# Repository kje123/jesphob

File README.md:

# jesphob
A fork of the PhobGCC project, created for the JESNET Gamecube Controller

If you've stumbled upon this, congrats! You have found this earlier than intended. This project is currently in the prototyping phase, so I do not recommend using this until I have done an official release, and I cannot help you if weird issues pop up.

If you wanna ask me questions or get involved, you can find me on Discord. My username is .kje

Original PhobGCC project here: https://github.com/PhobGCC

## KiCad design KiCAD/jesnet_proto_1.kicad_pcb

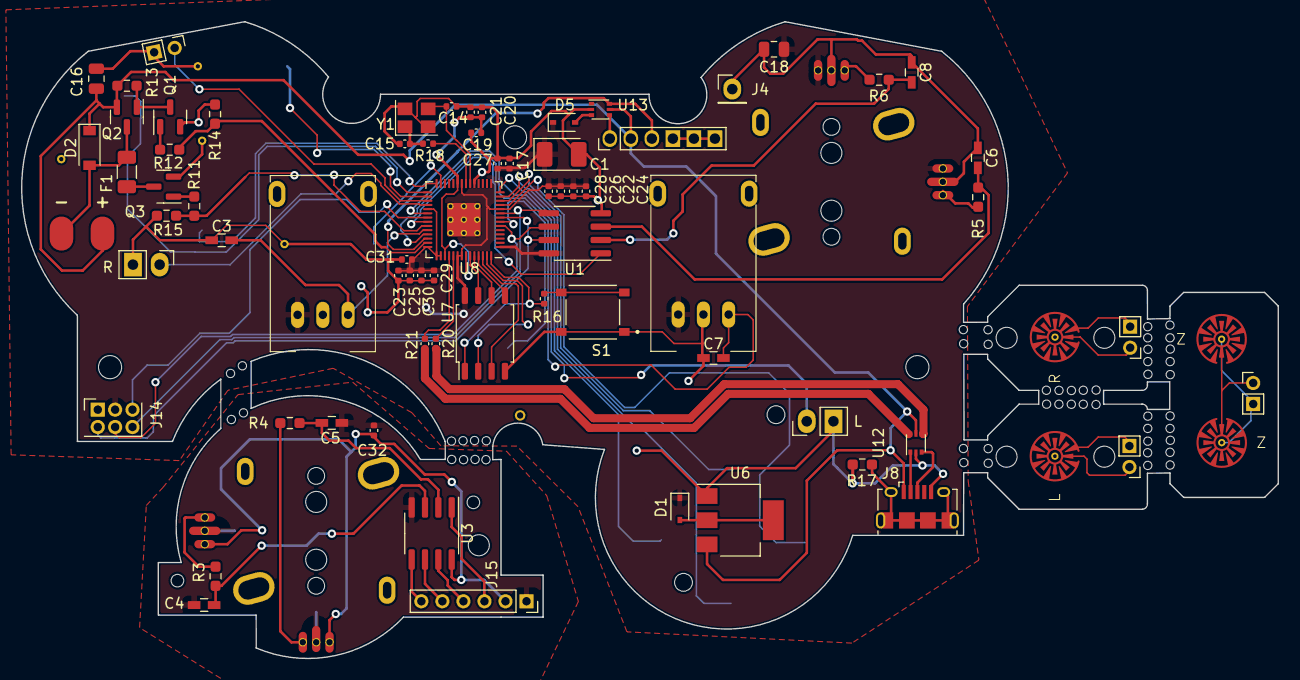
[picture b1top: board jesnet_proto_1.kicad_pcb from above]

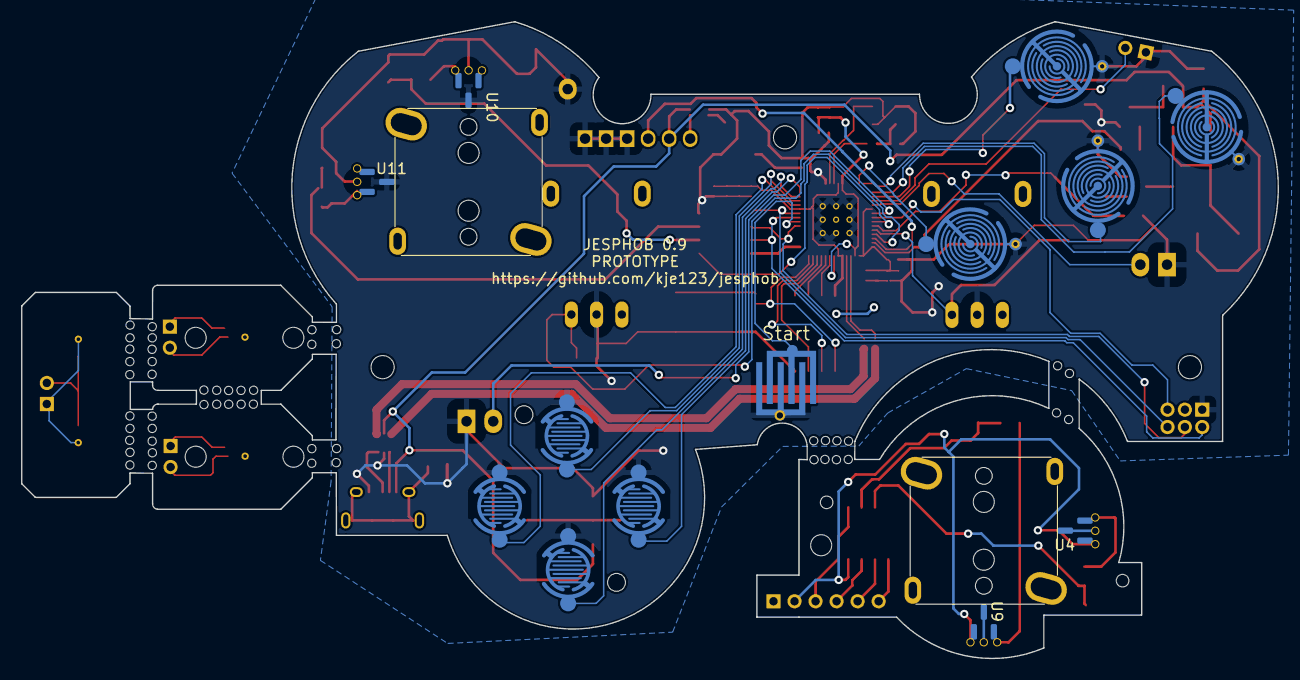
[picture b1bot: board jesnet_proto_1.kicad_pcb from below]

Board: 2 copper layers, 119.5 x 60.6 mm, 95 parts (15 on the bottom side), 65 nets.

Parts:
C1: 47u; CP_EIA-3528-12_Kemet-T_Pad1.50x2.35mm_HandSolder
C3, C4, C5, C6, C7, C8: 0.047u; C_0603_HandSoldering
C14, C15: 27p; C_0402_1005Metric
C16, C18: 10u; C_0805_2012Metric
C17, C19, C20, C22, C24, C25, C26, C27, C28, C29, C30, C31, C32: 100n; C_0402_1005Metric
C21, C23: 1u; C_0402_1005Metric
D1, D5: CUS10S30,H3F; D_SOD-323
D2: M7C; D_SOD-123
F1: Fuse; Fuse_1206_3216Metric
H5: 1.7mm; MountingHole_1.8mm
H9, H9#2, H9#3: 2.2mm; MountingHole_2.2mm
H10: 2mm; MountingHole_1.8mm
H10#2: 1.2mm; MountingHole_1.8mm
J1: Conn_01x06_Female; GCC_Header_Straight_1x06_Pitch2.00mm
J3, J3#2, J3#3, J3#4: Conn_01x02; PinHeader_1x02_P2.00mm_Horizontal
J4: Conn_01x01; PinHeader_1x01_P2.54mm_Vertical
J5: Rumble; rumble_pins
J8: USB_B_Micro; USB_Micro-B_Amphenol_10118194_Horizontal
J14, J15: Conn_01x06; PinSocket_1x06_P2.00mm_Vertical
Q1, Q3: Q_NMOS_GSD; SOT-23
Q2: Q_PMOS_GDS; SOT-23
R3, R4, R5, R6: 2k; R_0603_1608Metric_Pad0.98x0.95mm_HandSolder
R11, R12: 100R; R_0603_1608Metric_Pad0.98x0.95mm_HandSolder
R13, R14, R15: 10k; R_0603_1608Metric_Pad0.98x0.95mm_HandSolder
R16, R18: 1k; C_0402_1005Metric
R17: 100k; R_0603_1608Metric_Pad0.98x0.95mm_HandSolder
R20, R21: 27; C_0402_1005Metric
RV1, RV2: R_POT_MountingPin; GCC_Slider
S1: BOOTSEL; SW_TS-1187A-B-A-B
SW1: A; ABXY_Contact_Omron_Switch_Circley
SW2: L; Trigger_Contact
SW2#2, SW2#4: Z; Trigger_Contact
SW2#3: R; Trigger_Contact
SW2#5: B; ABXY_Contact_Omron_Switch_Circley
SW3: X; ABXY_Contact_Omron_Switch_Circley
SW4: Y; ABXY_Contact_Omron_Switch_Circley
SW5: Start; Start_Contact
SW6: L; Pin_Header_Straight_1x02_Pitch2.54mm
SW7: R; Pin_Header_Straight_1x02_Pitch2.54mm
SW9: Dleft; Dpad_Contact_TL3315NF_2_ZigZag
SW10: Dup; Dpad_Contact_TL3315NF_2_ZigZag
SW11: Dright; Dpad_Contact_TL3315NF_2_ZigZag
SW12: Ddown; Dpad_Contact_TL3315NF_2_ZigZag
U1, U3: MCP3202; SOIC-8_3.9x4.9mm_P1.27mm
U2: Stickbox_Assembly_Main; GCC_Stickbox_Hall_Only
U4, U9, U10, U11: DRV5055A3xDBZxQ1; SOT-23
U5: Stickbox_Assembly_CStick; GCC_Stickbox_Hall_Only
U6: AMS1117-3.3; SOT-223-3_TabPin2
U7: W25Q128JVS; SOIC-8_5.23x5.23mm_P1.27mm
U8: RP2040; RP2040-QFN-56
U12, U13: USBLC6-2P6; SOT-666
Y1: Crystal_GND24; Crystal_SMD_3225-4Pin_3.2x2.5mm

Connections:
+1V1: C19.1, C20.1, C21.1, U8.23 (DVDD), U8.45 (VREG_VOUT), U8.50 (DVDD)
+3V3: C1.1, C17.1, C18.1, C22.1, C23.1, C24.1, C25.1, C26.1, C27.1, C28.1, C29.1, C30.1, C31.1, D1.1 (K), D5.1 (K), J14.2, RV1.1 (V+), RV2.1 (V+), U1.8 (VDD/VREF), U2.1 (H1XV), U2.4 (H1YV), U7.8 (VCC), U8.1 (IOVDD), U8.10 (IOVDD), U8.22 (IOVDD), U8.33 (IOVDD), U8.42 (IOVDD), U8.43 (ADC_AVDD), U8.44 (VREG_IN), U8.48 (USB_VDD), U8.49 (IOVDD), U10.1 (VCC), U11.1 (VCC)
+5V: C16.1, D2.1 (K), J1.2, J5.1, J8.1 (VBUS), Q2.2 (S), R13.2, U6.3 (VI), U12.5 (VBUS), U13.5 (VBUS)
/A: SW1.1, U8.28 (GPIO17)
/B: SW2#5.1, U8.27 (GPIO16)
/Brake: R12.1, R14.2, U8.41 (GPIO29_ADC3)
/CLK: J14.4, U1.7 (CLK), U8.8 (GPIO6)
/CLK2: J15.4, U3.7 (CLK)
/CS1: U1.1 (~CS/SHDN), U8.36 (GPIO24)
/CS2: J14.3, U8.35 (GPIO23)
/CS2_2: J15.3, U3.1 (~CS/SHDN)
/C_x_filt: C5.1, R4.1, U3.2 (CH0)
/C_y_filt: C4.1, R3.1, U3.3 (CH1)
/Ddown: SW12.1, U8.13 (GPIO10)
/Din: J14.6, U1.5 (DIN), U8.9 (GPIO7)
/Din2: J15.6, U3.5 (DIN)
/Dleft: SW9.1, U8.11 (GPIO8)
/Dout: J14.5, U1.6 (DOUT), U8.6 (GPIO4)
/Dout2: J15.5, U3.6 (DOUT)
/Dright: SW11.1, U8.14 (GPIO11)
/Dup: SW10.1, U8.12 (GPIO9)
/GCC_3.3V: J1.1, U13.4 (I/O2)
/GCC_DATA: J1.3, U8.40 (GPIO28_ADC2), U13.6 (I/O1)
/GND_C: C4.2, C5.2, C32.2, J15.1, U3.4 (VSS), U4.3 (GND), U5.2 (H1XG), U5.5 (H1YG), U9.3 (GND)
/H1XS: R6.2, U2.3 (H1XS), U10.2 (OUT)
/H1YS: R5.2, U2.6 (H1YS), U11.2 (OUT)
/H2XS: R4.2, U5.3 (H1XS), U9.2 (OUT)
/H2YS: R3.2, U4.2 (OUT), U5.6 (H1YS)
/L: SW6.1, U8.34 (GPIO22)
/Lanalog: C7.1, RV1.3 (Signal), U8.39 (GPIO27_ADC1)
/QSPI_SCLK: U7.6 (CLK), U8.52 (QSPI_SCLK)
/QSPI_SD0: U7.5 (DI(IO0)), U8.53 (QSPI_SD0)
/QSPI_SD1: U7.2 (DO(IO1)), U8.55 (QSPI_SD1)
/QSPI_SD2: U7.3 (IO2), U8.54 (QSPI_SD2)
/QSPI_SD3: U7.7 (IO3), U8.51 (QSPI_SD3)
/QSPI_SS: R16.1, U7.1 (~CS), U8.56 (QSPI_SS)
/R: SW7.1, U8.32 (GPIO21)
/Ranalog: C3.1, RV2.3 (Signal), U8.38 (GPIO26_ADC0)
/Rumble: R11.1, R15.2, U8.37 (GPIO25)
/Start: SW5.1, U8.7 (GPIO5)
/Stick_x_filt: C8.1, R6.1, U1.2 (CH0)
/Stick_y_filt: C6.1, R5.1, U1.3 (CH1)
/USB_D+: R20.1, U12.4 (I/O2)
/USB_D+_Raw: J8.3 (D+), U12.3 (I/O2)
/USB_D-: R21.1, U12.6 (I/O1)
/USB_D-_Raw: J8.2 (D-), U12.1 (I/O1)
/X: SW3.1, U8.29 (GPIO18)
/XIN: C14.1, U8.20 (XIN), Y1.3
/XOUT: R18.1, U8.21 (XOUT)
/Y: SW4.1, U8.30 (GPIO19)
/Z: J3.2, U8.31 (GPIO20)
/~USB_BOOT: R16.2, S1.C, S1.D
GND: C1.2, C3.2, C6.2, C7.2, C8.2, C14.2, C15.2, C16.2, C17.2, C18.2, C19.2, C20.2, C21.2, C22.2, C23.2, C24.2, C25.2, C26.2, C27.2, C28.2, C29.2, C30.2, C31.2, J1.4, J1.5, J1.6, J3.1, J4.1, J8.5 (GND), J14.1, Q1.2 (S), Q3.2 (S), R14.1, R15.1, R17.2, RV1.2 (GND), RV2.2 (GND), S1.A, S1.B, SW1.2, SW2#5.2, SW3.2, SW4.2, SW5.2, SW6.2, SW7.2, SW9.2, SW10.2, SW11.2, SW12.2, U1.4 (VSS), U2.2 (H1XG), U2.5 (H1YG), U6.1 (GND), U7.4 (GND), U8.19 (TESTEN), U8.57 (GND), U10.3 (GND), U11.3 (GND), U12.2 (GND), U13.2 (GND), Y1.2, Y1.4
unnamed: C15.1, R18.2, Y1.1
unnamed: D1.2 (A), U6.2 (VO)
unnamed: D2.2 (A), F1.1, J5.2, Q2.3 (D)
unnamed: D5.2 (A), U13.3 (I/O2)
unnamed: F1.2, Q3.3 (D)
unnamed: J8.6 (Shield), R17.1
unnamed: Q1.1 (G), R12.2
unnamed: Q1.3 (D), Q2.1 (G), R13.1
unnamed: Q3.1 (G), R11.2
unnamed: R20.2, U8.47 (USB_DP)
unnamed: R21.2, U8.46 (USB_DM)
VCC: C32.1, J15.2, U3.8 (VDD/VREF), U4.1 (VCC), U5.1 (H1XV), U5.4 (H1YV), U9.1 (VCC)

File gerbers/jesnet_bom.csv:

Comment,Designator,Footprint,LCSC Part #
47u Polarized capacitor,C1,CP_EIA-3528-12_Kemet-T_Pad1.50x2.35mm_HandSolder,
0.047u Unpolarized capacitor,"C3,C4,C5,C6,C7,C8",C_0603_HandSoldering,
27p Unpolarized capacitor,"C14,C15",C_0402_1005Metric,
10u Unpolarized capacitor,"C16,C18",C_0805_2012Metric,
100n Unpolarized capacitor,"C17,C19,C20,C22,C24,C25,C26,C27,C28,C29,C30,C31,C32",C_0402_1005Metric,
1u Unpolarized capacitor,"C21,C23",C_0402_1005Metric,
"CUS10S30,H3F 20V 0.5A Schottky Power Rectifier Diode, SOD-123","D1,D5",D_SOD-323,
M7C Schottky diode,D2,D_SOD-123,
Fuse Fuse,F1,Fuse_1206_3216Metric,
5.2mm Mounting Hole without connection,H1,MountingHole_5.2mm,
Slot Mounting Hole without connection,H2,Slot,
2mm Mounting Hole without connection,"H3,H4",MountingHole_2.0mm,
1.8mm Mounting Hole without connection,"H5,H6",MountingHole_1.8mm,
2.4mm Mounting Hole without connection,H7,MountingHole_2.4mm,
2.2mm Mounting Hole without connection,"H8,H9",MountingHole_2.2mm,
MountingHole Mounting Hole without connection,H10,MountingHole_1.8mm,
MountingHole Mounting Hole without connection,H11,MountingHole_5.2mm,
MountingHole Mounting Hole without connection,"H12,H13",MountingHole_2.0mm,
MouseBite Mounting Hole without connection,H14,breakaway-mousebites-double-v2-small,
MouseBite Mounting Hole without connection,H15,breakaway-mousebites-double-v2-large,
"Conn_01x06_Female Generic connector, single row, 01x06, script generated (kicad-library-utils/schlib/autogen/connector/)",J1,GCC_Header_Straight_1x06_Pitch2.00mm,
"Conn_01x02 Generic connector, single row, 01x02, script generated (kicad-library-utils/schlib/autogen/connector/)","J2,J11",PinHeader_1x02_P2.00mm_Vertical,
"Conn_01x02 Generic connector, single row, 01x02, script generated (kicad-library-utils/schlib/autogen/connector/)",J3,PinHeader_1x02_P2.00mm_Horizontal,
"Conn_01x01 Generic connector, single row, 01x01, script generated (kicad-library-utils/schlib/autogen/connector/)",J4,PinHeader_1x01_P2.54mm_Vertical,
"Rumble Generic connector, single row, 01x02, script generated (kicad-library-utils/schlib/autogen/connector/)",J5,rumble_pins,
"Conn_01x06 Generic connector, single row, 01x06, script generated (kicad-library-utils/schlib/autogen/connector/)",J6,PinSocket_1x06_P2.00mm_Vertical,
USB_B_Micro USB Micro Type B connector,J8,USB_Micro-B_Amphenol_10118194_Horizontal,
"Conn_01x06 Generic connector, single row, 01x06, script generated (kicad-library-utils/schlib/autogen/connector/)","J14,J15",PinSocket_1x06_P2.00mm_Vertical,
"Q_NMOS_GSD N-MOSFET transistor, gate/source/drain","Q1,Q3",SOT-23,
"Q_PMOS_GDS P-MOSFET transistor, gate/source/drain",Q2,SOT-23,
180 Resistor,"R1,R2,R7,R8,R9",R_0402_1005Metric,
2k Resistor,"R3,R4,R5,R6",R_0603_1608Metric_Pad0.98x0.95mm_HandSolder,
316 Resistor,"R10,R19,R24,R25",R_0402_1005Metric,
100R Resistor,"R11,R12",R_0603_1608Metric_Pad0.98x0.95mm_HandSolder,
10k Resistor,"R13,R14,R15",R_0603_1608Metric_Pad0.98x0.95mm_HandSolder,
1k Resistor,"R16,R18",C_0402_1005Metric,
100k Resistor,R17,R_0603_1608Metric_Pad0.98x0.95mm_HandSolder,
27 Resistor,"R20,R21",C_0402_1005Metric,
R_POT_MountingPin ,"RV1,RV2",GCC_Slider,
BOOTSEL ,S1,SW_TS-1187A-B-A-B,
"A Push button switch, generic, two pins",SW1,ABXY_Contact_Omron_Switch_Circley,
"B Push button switch, generic, two pins",SW2,ABXY_Contact_Omron_Switch_Circley,
"X Push button switch, generic, two pins",SW3,ABXY_Contact_Omron_Switch_Circley,
"Y Push button switch, generic, two pins",SW4,ABXY_Contact_Omron_Switch_Circley,
"Start Push button switch, generic, two pins",SW5,Start_Contact,
"L Push button switch, generic, two pins",SW6,Pin_Header_Straight_1x02_Pitch2.54mm,
"R Push button switch, generic, two pins",SW7,Pin_Header_Straight_1x02_Pitch2.54mm,
"Z 1x DIP Switch, Single Pole Single Throw (SPST) switch, small symbol",SW8,Z_Switch_Edge_Omron,
"Dleft Push button switch, generic, two pins",SW9,Dpad_Contact_TL3315NF_2_ZigZag,
"Dup Push button switch, generic, two pins",SW10,Dpad_Contact_TL3315NF_2_ZigZag,
"Dright Push button switch, generic, two pins",SW11,Dpad_Contact_TL3315NF_2_ZigZag,
"Ddown Push button switch, generic, two pins",SW12,Dpad_Contact_TL3315NF_2_ZigZag,
MCP3202 Dual Channel 10-Bit A/D Converter with SPI Serial Interface,"U1,U3",SOIC-8_3.9x4.9mm_P1.27mm,
Stickbox_Assembly_Main ,U2,GCC_Stickbox_Hall_Only,
"DRV5055A3xDBZxQ1 50 mV/mT,±42-mT, 20-kHz, 3.3/5V, SOT-23","U4,U9,U10,U11",SOT-23,
Stickbox_Assembly_CStick ,U5,GCC_Stickbox_Hall_Only,
"AMS1117-3.3 1A Low Dropout regulator, positive, 3.3V fixed output, SOT-223",U6,SOT-223-3_TabPin2,
"W25Q128JVS 128Mb Serial Flash Memory, Standard/Dual/Quad SPI, SOIC-8",U7,SOIC-8_5.23x5.23mm_P1.27mm,
RP2040 ,U8,RP2040-QFN-56,
"USBLC6-2P6 Very low capacitance ESD protection diode, 2 data-line, SOT-666","U12,U13",SOT-666,
"Crystal_GND24 Four pin crystal, GND on pins 2 and 4",Y1,Crystal_SMD_3225-4Pin_3.2x2.5mm,

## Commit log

2023-07-20 Update LICENSE to CERN
2023-07-20 added prototype files
2023-07-20 added 3d models to footprints, reversed polarity on trigger sliders
2023-07-20 rerouted some traces, fixed 3d model of c0603
2023-07-21 added 3d models, adjusted stickbox positioning
2023-09-27 final stickbox adjustments
2024-01-05 prototype gerbers bom pos generated
2024-01-05 deleted bad bom
